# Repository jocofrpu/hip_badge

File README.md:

# hip_badge
Hardware for the Hip Badge

The HIP Badge is a small Badge for  "Hack im Pott" it is a round PCB with an 5x11 LED matrix powered by an ATmega328.

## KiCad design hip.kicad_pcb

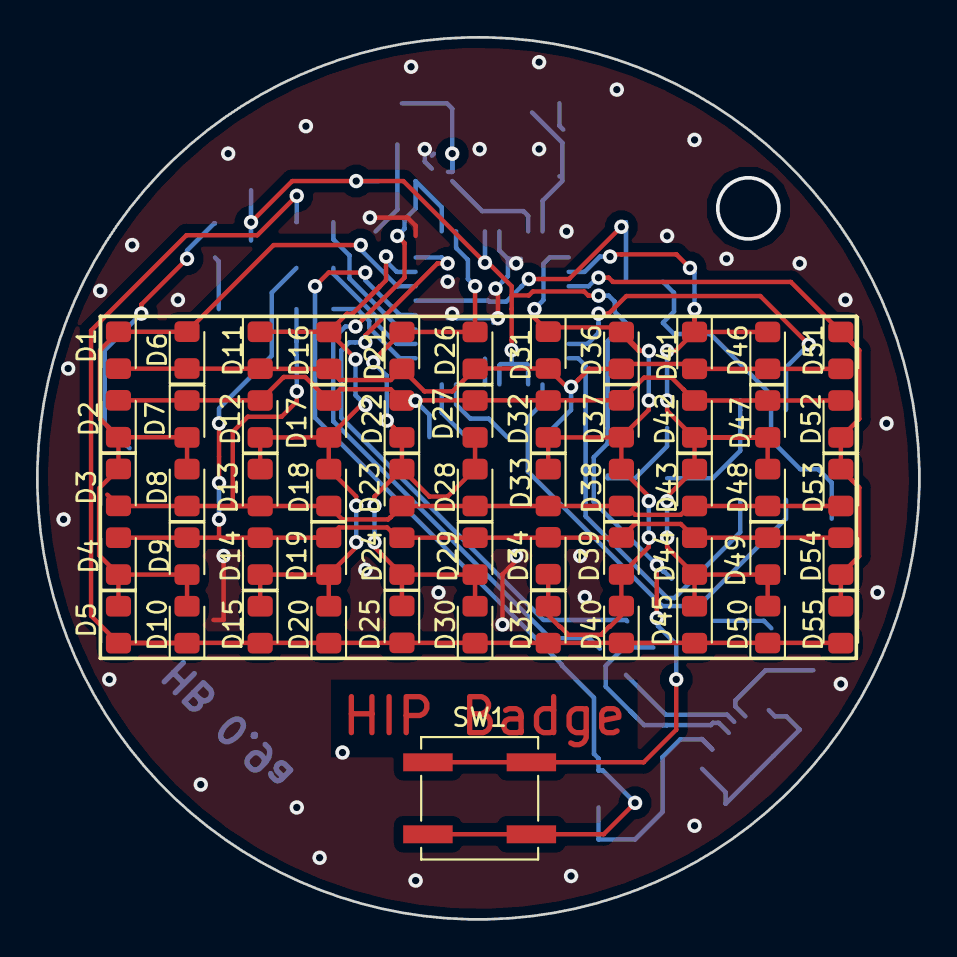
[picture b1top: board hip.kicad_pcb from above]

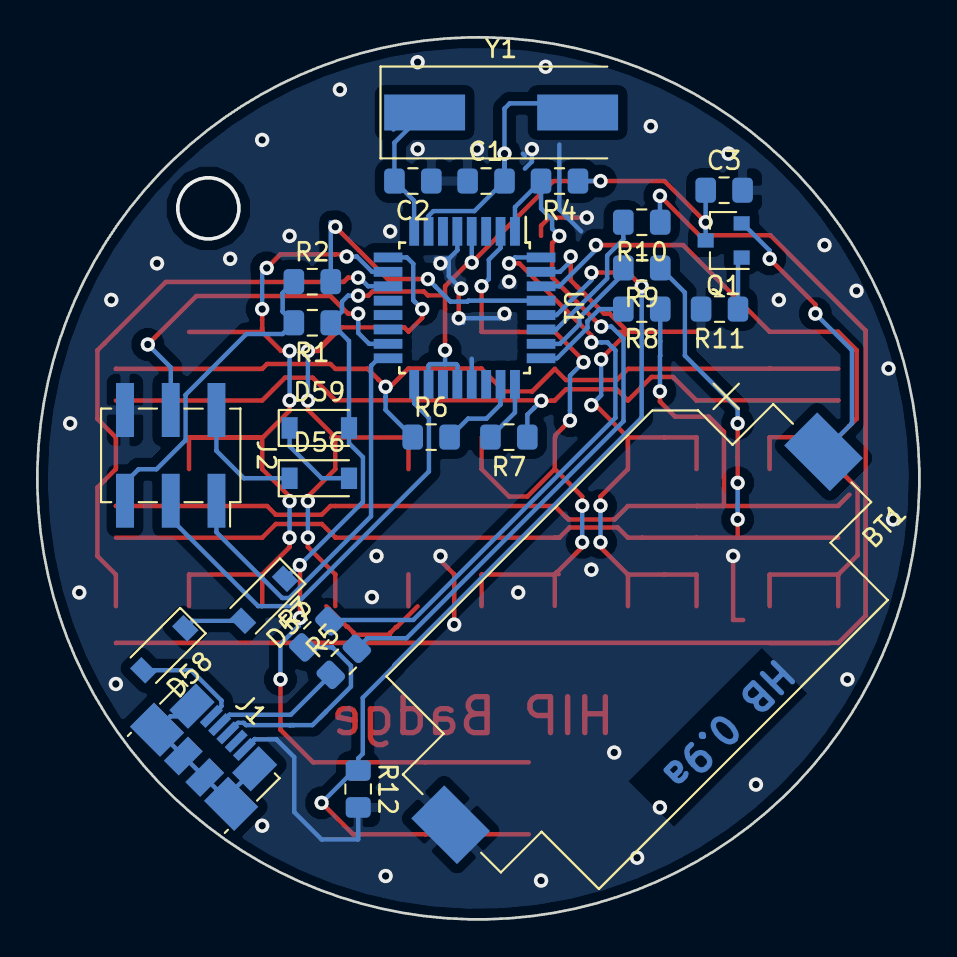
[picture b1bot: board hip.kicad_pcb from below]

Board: 2 copper layers, 49.0 x 49.0 mm, 81 parts (25 on the bottom side), 36 nets.

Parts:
BT1: Battery_Cell; BatteryHolder_Keystone_1060_1x2032
C1, C2: 18p; C_0805_2012Metric_Pad1.15x1.40mm_HandSolder
C3: C; C_0805_2012Metric_Pad1.15x1.40mm_HandSolder
D1, D2, D3, D4, D5, D6, D7, D8, D9, D10, D11, D12, D13, D14, D15, D16, D17, D18, D19, D20, D21, D22, D23, D24, D25, D26, D27, D28, D29, D30, D31, D32, D33, D34, D35, D36, D37, D38, D39, D40, D41, D42, D43, D44, D45, D46, D47, D48, D49, D50, D51, D52, D53, D54, D55: LED; LED_0805_2012Metric_Pad1.15x1.40mm_HandSolder
D56, D57, D58, D59: 1N4148W; D_SOD-123
J1: USB_B_Micro; USB_Micro-B_Molex_47346-0001
J2: Conn_02x03_Odd_Even; PinSocket_2x03_P2.54mm_Vertical_SMD
Q1: BSS83P; SOT-23
R1, R6, R7, R8, R9, R10, R11, R12: R; R_0805_2012Metric_Pad1.15x1.40mm_HandSolder
R2, R4: 1,5k; R_0805_2012Metric_Pad1.15x1.40mm_HandSolder
R3, R5: 68; R_0805_2012Metric_Pad1.15x1.40mm_HandSolder
SW1: SW_Push; SW_SPST_B3SL-1002P
U1: ATmega328PB-AU; TQFP-32_7x7mm_P0.8mm
Y1: Crystal; Crystal_SMD_HC49-SD

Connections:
+3V3: C3.1, D57.1, D59.2, Q1.3, R1.1, R4.1, SW1.1, U1.4, U1.18, U1.20
D0: R6.2, U1.23
D1: R7.2, U1.24
D2: R8.2, U1.25
D3: R9.2, U1.26
D4: R10.2, U1.27
E0: D1.1, D2.1, D3.1, D4.1, D5.1, D6.2, D7.2, D8.2, D9.2, D10.2, U1.30
E1: D11.1, D12.1, D13.1, D14.1, D15.1, D16.2, D17.2, D18.2, D19.2, D20.2, U1.31
E2: D21.1, D22.1, D23.1, D24.1, D25.1, D26.2, D27.2, D28.2, D29.2, D30.2, U1.2
E3: D31.1, D32.1, D33.1, D34.1, D35.1, D36.2, D37.2, D38.2, D39.2, D40.2, U1.9
E4: D41.1, D42.1, D43.1, D44.1, D45.1, D46.2, D47.2, D48.2, D49.2, D50.2, U1.10
E5: D51.1, D52.1, D53.1, D54.1, D55.1, U1.11
GND: BT1.2, C1.1, C2.1, C3.2, J1.5, J2.6, R11.2, R12.2, U1.5, U1.21
MISO: J2.1, U1.16
MOSI: J2.4, U1.15
unnamed: BT1.1, Q1.2
unnamed: C1.2, U1.7, Y1.2
unnamed: C2.2, U1.8, Y1.1
unnamed: D1.2, D6.1, D11.2, D16.1, D21.2, D26.1, D31.2, D36.1, D41.2, D46.1, D51.2, R6.1
unnamed: D5.2, D10.1, D15.2, D20.1, D25.2, D30.1, D35.2, D40.1, D45.2, D50.1, D55.2, R10.1
unnamed: D2.2, D7.1, D12.2, D17.1, D22.2, D27.1, D32.2, D37.1, D42.2, D47.1, D52.2, R7.1
unnamed: D3.2, D8.1, D13.2, D18.1, D23.2, D28.1, D33.2, D38.1, D43.2, D48.1, D53.2, R8.1
unnamed: D4.2, D9.1, D14.2, D19.1, D24.2, D29.1, D34.2, D39.1, D44.2, D49.1, D54.2, R9.1
unnamed: D56.1, J2.2
unnamed: D56.2, D59.1
unnamed: D57.2, D58.1
unnamed: D58.2, J1.1
unnamed: J1.2, R5.1
unnamed: J1.3, R3.1
unnamed: Q1.1, R11.1
unnamed: R2.2, U1.29
unnamed: R3.2, U1.32
unnamed: R4.2, R5.2, U1.1
SW: R12.1, SW1.2, U1.28
res: J2.5, R1.2, R2.1
sck: J2.3, U1.17
